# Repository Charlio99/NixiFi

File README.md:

# NixiFi

NixiFi is an all in one WiFi Nixie NTP Clock board, only you have to do is to solder the components and upload the code!.

# Features

  - ESP8266 based (Arduino IDE code).
  - NTP Time.
  - No spare PSUs messing around, the 170v output is handled by a small smd PSU (link in BOM).
  - 5V Powered and it only draws 1.5-2W.
  - Oled display and encoder to configure zone, auto DST, the cathode poisoning prevention, auto shutdown between specific hours, etc.
  - Go over all numbers at specific time to avoid cathode poisoning (can be configured with the OLED display)
  - Plug and play. Once you upload the code, a WiFi network will appear, connect to it following the instructions in the OLED display.

### BOM

I mainly use JLCPCB and LCSC for PCB and components.

| Component | Quantity | Link | Price |
| ------ | ------ | ------ | ------ |
| ESP-12E | 1 | https://lcsc.com/product-detail/WIFI-Modules_ESP-12E_C89297.html | $2.2 |
| 170v PSU | 1 | https://www.ebay.es/itm/141728921034 | $9.99 |
| 100nF | 4 | https://lcsc.com/product-detail/Multilayer-Ceramic-Capacitors-MLCC-SMD-SMT_SAMSUNG_CL21B104KBCNNNC_100nF-104-10-50V_C1711.html | $0.46 |
| 1uF | 2 | https://lcsc.com/product-detail/Multilayer-Ceramic-Capacitors-MLCC-SMD-SMT_1uF-106-10-16V_C94122.html | $0.3 |
| 10uF Tantalum | 2 | https://lcsc.com/product-detail/Tantalum-Capacitors_AVX_TAJA106K010RNJ_10uF-106-10-10V_C7177.html | $0.24 |
| USB Micro B | 1 | https://lcsc.com/product-detail/Micro-USB-Connectors_Korean-Hroparts-Elec-U-F-M5DD-Y-1_C91467.html | $0.17 |
| OLED 0.96" | 1 | https://es.aliexpress.com/item/32713614136.html | $1.76 |
| Encoder | 1 | https://es.aliexpress.com/item/Rotary-Encoder-Module-Brick-Sensor-Development-for-arduino-KY-040/32462116984.html | $0.68 |
| 2N7002 | 4 | https://lcsc.com/product-detail/MOSFET_ON-Semicon_2N7002LT1G_ON-Semicon-ON-2N7002LT1G_C16338.html | $0.5 |
| 27K | 6 | https://lcsc.com/product-detail/Chip-Resistor-Surface-Mount_27KR-2702-1_C175357.html | $0.4 |
| 100K | 2 | https://lcsc.com/product-detail/Chip-Resistor-Surface-Mount_100KR-1003-1_C147046.html | $0.85 |
| 10K | 13 | https://lcsc.com/product-detail/Chip-Resistor-Surface-Mount_10KR-103-5_C100047.html | $0.14 |
| Header 4 pins | 3 | https://es.aliexpress.com/item/32847365702.html | $0.77 |
| HV5622 | 2 | https://www.arrow.com/en/products/hv5622pg-g/microchip-technology | $12.32 |
| AMS1117-3.3 | 1 | https://lcsc.com/product-detail/Low-Dropout-Regulators-LDO_AMS_AMS1117-3-3_AMS1117-3-3_C6186.html | $0.57 |
| | | **TOTAL** | **$31.35**|

Take in account that some components must be ordered in larger batches that the quantity needed and shipping costs are not included in the BOM.

### Todos

 - Adapt PCB for making it compatible with IN-8-2 without the need of modifying the IN-8-2. (At the moment it can be done cutting the dot pin and bending pin 1 to be in place of the dot.)
 - Improve README
 
### License

GNU Public License 3.0
Please, if you pretend to use it for comercial uses, contact me before

### Photos

**Open Source FTW, Hell Yeah!**

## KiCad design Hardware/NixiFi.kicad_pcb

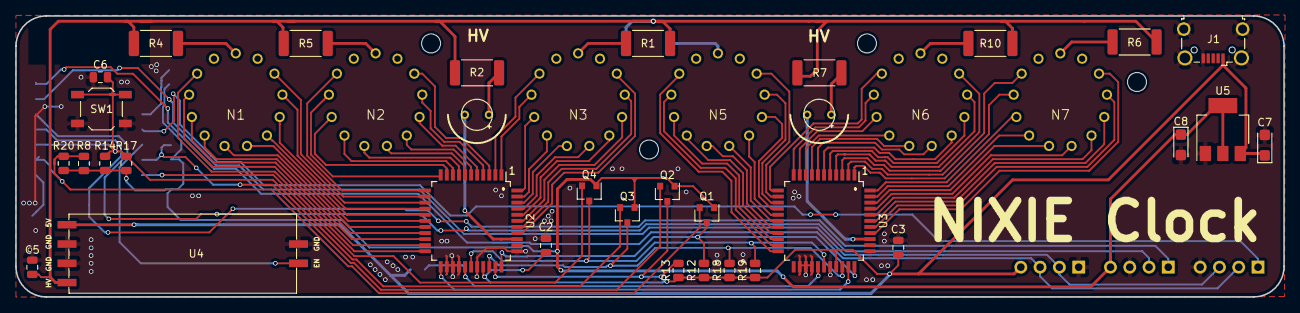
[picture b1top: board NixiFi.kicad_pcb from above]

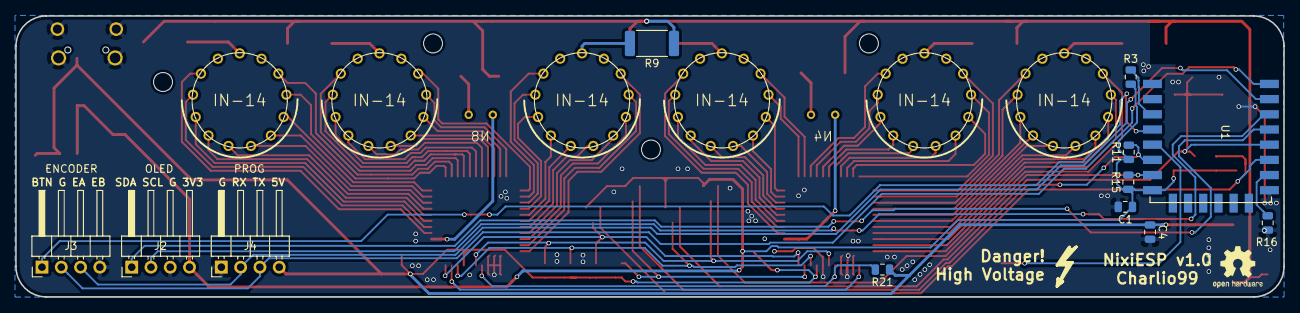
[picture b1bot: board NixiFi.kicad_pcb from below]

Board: 2 copper layers, 167.0 x 37.0 mm, 51 parts (18 on the bottom side), 92 nets.

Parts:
C1, C6: 100nF; C_0805_2012Metric
C2, C3: 1uF; C_0805_2012Metric
C4, C5: 0.1uF; C_0805_2012Metric
C7, C8: C; CP_EIA-3216-12_Kemet-S
J1: USB_B_Micro; USB_Micro-B_Wuerth_629105150521_CircularHoles
J2: OLED; PinHeader_1x04_P2.54mm_Horizontal
J3: ENCODER; PinHeader_1x04_P2.54mm_Horizontal
J4: PROG; PinHeader_1x04_P2.54mm_Horizontal
N1, N2, N3, N5, N6, N7: IN-14; russian-nixies-IN-14
N4, N8: IN-3; russian-nixies-IN-3
Q1, Q2, Q3, Q4: 2N7002; SOT-23
R1, R4, R5, R6, R9, R10: 27K; R_2512_6332Metric
R2, R7: 100K; R_2512_6332Metric
R3, R8, R11, R12, R13, R14, R15, R16, R17, R18, R19, R20, R21: 10K; R_0805_2012Metric
SW1: PROG_MODE; SW_SPST_TL3342
U1: ESP-12E; ESP-12E_SMD
U2, U3: HV5622; PQFP-44_10x10mm_P0.8mm
U4: PSU; TypeD-PowerSupply
U5: AMS1117-3.3; SOT-223-3_TabPin2

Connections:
+3V3: C1.1, C8.1, J2.4, Q1.1, Q2.1, Q3.1, Q4.1, R3.2, R8.1, R11.1, R14.1, R15.1, R17.1, R20.1, U1.8, U5.2
+5V: C2.1, C3.1, C4.1, C7.1, J1.1, J4.4, R12.1, R13.1, R18.1, R19.1, R21.1, U2.30, U3.30, U4.1, U5.3
/BL: Q1.3, R12.2, U2.33, U3.33
/BL_PIN: Q1.2, R8.2, R20.2, U1.11
/BTN: J3.1, U1.4
/CLK: Q4.3, R19.2, U2.28, U3.28
/CLK_PIN: Q4.2, R15.2, U1.7
/DATA_IN: Q2.3, R13.2, U2.32
/DATA_IN_PIN: Q2.2, R11.2, U1.6
/ENABLE: U1.5, U4.6
/GPIO15: R16.1, U1.10
/LE: Q3.3, R18.2, U2.31, U3.31
/LE_PIN: C6.2, Q3.2, R14.2, R17.2, SW1.1, U1.12
/RXD: J3.3, J4.2, U1.15
/SCL: J2.2, U1.14
/SDA: J2.1, U1.13
/TXD: J3.2, J4.3, U1.16
GND: C1.2, C2.2, C3.2, C4.2, C5.1, C6.1, C7.2, C8.2, J1.5, J1.6, J2.3, J3.4, J4.1, R16.2, SW1.2, U1.9, U2.24, U2.25, U2.26, U2.29, U2.34, U3.24, U3.25, U3.26, U3.29, U3.34, U4.2, U4.3, U4.5, U5.1
HT: C5.2, R1.1, R2.1, R4.1, R5.1, R6.1, R7.1, R9.1, R10.1, U4.4
unnamed: N1.0, U2.13
unnamed: N1.1, U2.22
unnamed: N1.2, U2.21
unnamed: N1.3, U2.20
unnamed: N1.4, U2.19
unnamed: N1.5, U2.18
unnamed: N1.6, U2.17
unnamed: N1.7, U2.16
unnamed: N1.8, U2.15
unnamed: N1.9, U2.14
unnamed: N1.A, R4.2
unnamed: N2.0, U2.3
unnamed: N2.1, U2.12
unnamed: N2.2, U2.11
unnamed: N2.3, U2.10
unnamed: N2.4, U2.9
unnamed: N2.5, U2.8
unnamed: N2.6, U2.7
unnamed: N2.7, U2.6
unnamed: N2.8, U2.5
unnamed: N2.9, U2.4
unnamed: N2.A, R5.2
unnamed: N3.0, U2.37
unnamed: N3.1, U2.2
unnamed: N3.2, U2.1
unnamed: N3.3, U2.44
unnamed: N3.4, U2.43
unnamed: N3.5, U2.42
unnamed: N3.6, U2.41
unnamed: N3.7, U2.40
unnamed: N3.8, U2.39
unnamed: N3.9, U2.38
unnamed: N3.A, R1.2
unnamed: N4.A, R2.2
unnamed: N4.K, U2.36
unnamed: N5.0, U3.13
unnamed: N5.1, U3.22
unnamed: N5.2, U3.21
unnamed: N5.3, U3.20
unnamed: N5.4, U3.19
unnamed: N5.5, U3.18
unnamed: N5.6, U3.17
unnamed: N5.7, U3.16
unnamed: N5.8, U3.15
unnamed: N5.9, U3.14
unnamed: N5.A, R9.2
unnamed: N6.0, U3.3
unnamed: N6.1, U3.12
unnamed: N6.2, U3.11
unnamed: N6.3, U3.10
unnamed: N6.4, U3.9
unnamed: N6.5, U3.8
unnamed: N6.6, U3.7
unnamed: N6.7, U3.6
unnamed: N6.8, U3.5
unnamed: N6.9, U3.4
unnamed: N6.A, R10.2
unnamed: N7.0, U3.37
unnamed: N7.1, U3.2
unnamed: N7.2, U3.1
unnamed: N7.3, U3.44
unnamed: N7.4, U3.43
unnamed: N7.5, U3.42
unnamed: N7.6, U3.41
unnamed: N7.7, U3.40
unnamed: N7.8, U3.39
unnamed: N7.9, U3.38
unnamed: N7.A, R6.2
unnamed: N8.A, R7.2
unnamed: N8.K, U3.36
unnamed: R3.1, U1.3
unnamed: R21.2, U2.27, U3.27
unnamed: U2.23, U3.32

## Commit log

2019-04-19 Working version rev1.0
2019-05-11 Added renders
2019-05-11 Fully working version and tested
2019-05-12 Added real images of the rev1.0
2019-05-12 Fixed images name

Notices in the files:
README.md:
GPL license
